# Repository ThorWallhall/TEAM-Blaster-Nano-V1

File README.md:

# T.E.A.M. Blaster Nano V1

**Open-source prop electronics kit for makers, cosplayers, and fandom builders.**  
**Open-Source-Elektronikkit für Maker, Cosplayer und Fandom-Bastler.**

[🇬🇧 English](#english) · [🇩🇪 Deutsch](#deutsch)

---

## English

### Overview

The T.E.A.M. Blaster Nano V1 is a compact all-in-one electronics board for
button-triggered sound and light effects in DIY props — fandom blasters,
sci-fi phasers, lightsabers and similar projects. A single button press plays
an audio sample through the onboard DFPlayer Mini while flashing an LED in sync.

### Features

- Button-triggered audio playback with synchronized LED effect
- Integrated Li-Ion battery charging over USB-C (**TP4056**)
- Battery protection circuit (**DW01A + FS8205A** dual MOSFET)
- Boost converter for a stable supply rail (**MT3608**)
- **ATmega328P-AU** microcontroller — Arduino Nano compatible
- Onboard USB-UART bridge (**CH340G**) — flash firmware directly via USB-C
- Compact form factor with JST-XH connectors for battery, speaker, button, LED

### Hardware

| Block               | Part                     | Package       |
|---------------------|--------------------------|---------------|
| Microcontroller     | ATmega328P-AU            | TQFP-32       |
| Audio player        | DFPlayer Mini (DFR0299)  | module        |
| Battery charger     | TP4056                   | SOIC-8-1EP    |
| Battery protection  | DW01A + FS8205A          | SOT-23-6 + TSSOP-8 |
| Boost converter     | MT3608                   | SOT-23-6      |
| USB-UART bridge     | CH340G                   | SOIC-16       |
| USB input           | USB-C (GCT USB4085)      | —             |

Full bill of materials in `Dokumentation/`.

### Repository Structure

```
├── Code T.E.A.M. - Blaster Nano V1/   → firmware (PlatformIO / Arduino)
├── Dokumentation/                     → BOM, datasheets
├── KiCAD/                             → schematic + PCB design files
├── ASSEMBLY.md                        → ⚠️ assembly & safety notes
└── README.md                          → this file
```

### Firmware

Written in C++11 for the Arduino framework. Builds with either the Arduino IDE
or PlatformIO.

Dependencies:

- `Arduino.h` *(core)*
- `SoftwareSerial.h` *(core)*
- `DFRobotDFPlayerMini` *(install via library manager)*

### ⚠️ Assembly

**Before first power-on, read [`ASSEMBLY.md`](ASSEMBLY.md).**
It contains critical polarity information for the JST-XH connectors —
wrong polarity can destroy the battery cell or the protection circuit.

### License

MIT License — see the `LICENSE` file for details.

### Author

T.E.A.M. — *for your fandom* · © 2026

---

## Deutsch

### Überblick

Der T.E.A.M. Blaster Nano V1 ist eine kompakte All-in-One-Elektronikplatine
für taster-ausgelöste Sound- und Lichteffekte in Eigenbau-Props — Fandom-Blaster,
Sci-Fi-Phaser, Lichtschwerter und ähnliche Projekte. Ein Tastendruck spielt ein
Audio-Sample über das integrierte DFPlayer-Mini-Modul und lässt synchron dazu
eine LED aufleuchten.

### Funktionen

- Taster-ausgelöste Audio-Wiedergabe mit synchronem LED-Effekt
- Integrierte Li-Ion-Akkuladung über USB-C (**TP4056**)
- Schutzschaltung für den Akku (**DW01A + FS8205A** Dual-MOSFET)
- Step-Up-Wandler für stabile Versorgungsspannung (**MT3608**)
- **ATmega328P-AU** Mikrocontroller — Arduino-Nano-kompatibel
- Integrierter USB-UART-Bridge (**CH340G**) — Firmware direkt über USB-C flashen
- Kompaktes Format mit JST-XH-Steckern für Akku, Lautsprecher, Taster, LED

### Hardware

| Block               | Bauteil                  | Gehäuse       |
|---------------------|--------------------------|---------------|
| Mikrocontroller     | ATmega328P-AU            | TQFP-32       |
| Audio-Player        | DFPlayer Mini (DFR0299)  | Modul         |
| Akku-Lader          | TP4056                   | SOIC-8-1EP    |
| Akku-Schutz         | DW01A + FS8205A          | SOT-23-6 + TSSOP-8 |
| Step-Up-Wandler     | MT3608                   | SOT-23-6      |
| USB-UART-Bridge     | CH340G                   | SOIC-16       |
| USB-Eingang         | USB-C (GCT USB4085)      | —             |

Die vollständige Stückliste liegt im Ordner `Dokumentation/`.

### Repository-Struktur

```
├── Code T.E.A.M. - Blaster Nano V1/   → Firmware (PlatformIO / Arduino)
├── Dokumentation/                     → Stückliste, Datenblätter
├── KiCAD/                             → Schaltplan + PCB-Entwurfsdaten
├── ASSEMBLY.md                        → ⚠️ Montage- & Sicherheitshinweise
└── README.md                          → diese Datei
```

### Firmware

Geschrieben in C++11 für das Arduino-Framework. Lässt sich sowohl mit der
Arduino IDE als auch mit PlatformIO bauen.

Abhängigkeiten:

- `Arduino.h` *(Kern)*
- `SoftwareSerial.h` *(Kern)*
- `DFRobotDFPlayerMini` *(über Library Manager installieren)*

### ⚠️ Montage

**Vor dem ersten Einschalten unbedingt [`ASSEMBLY.md`](ASSEMBLY.md) lesen.**
Dort stehen wichtige Polungshinweise zu den JST-XH-Steckern —
falsche Polung kann den Akku oder die Schutzschaltung zerstören.

### Lizenz

MIT-Lizenz — Details in der Datei `LICENSE`.

### Autor

T.E.A.M. — *for your fandom* · © 2026

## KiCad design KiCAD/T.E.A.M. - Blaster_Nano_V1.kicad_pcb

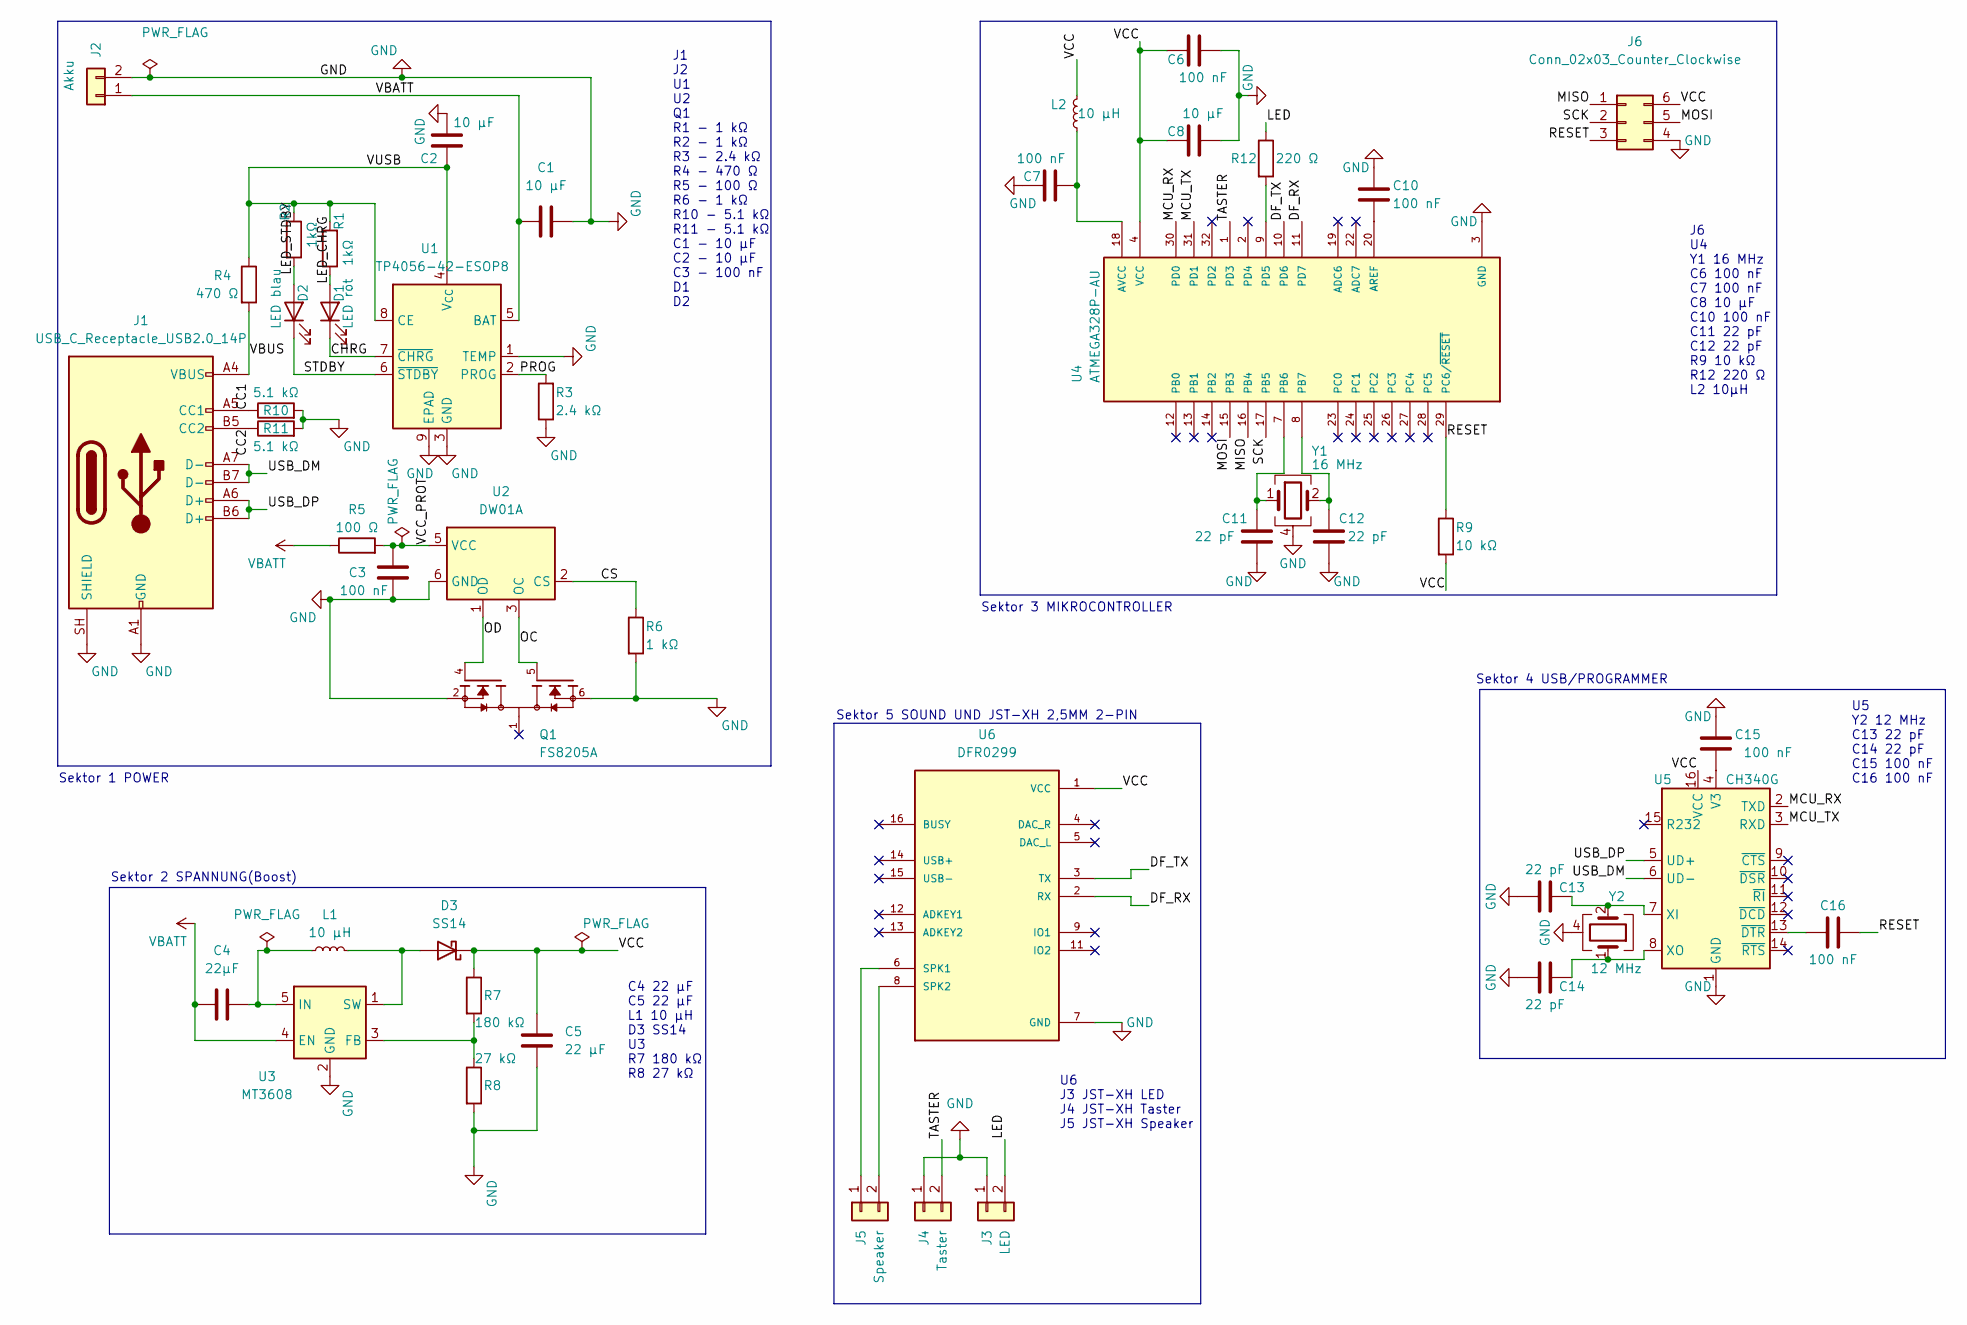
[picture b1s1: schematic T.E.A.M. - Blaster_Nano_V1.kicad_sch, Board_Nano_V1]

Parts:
C1, C2, C8: 10 µF; C_0805_2012Metric
C3, C6, C7, C10, C15, C16: 100 nF; C_0402_1005Metric
C4: 22µF; C_0805_2012Metric
C5: 22 µF; C_0805_2012Metric
C11, C12, C13, C14: 22 pF; C_0402_1005Metric
D1: LED rot; LED_0805_2012Metric
D2: LED blau; LED_0805_2012Metric
D3: SS14; D_SMA
J1: USB_C_Receptacle_USB2.0_14P; USB_C_Receptacle_GCT_USB4085
J2: Akku; JST_XH_B2B-XH-A_1x02_P2.50mm_Vertical
J3: LED; JST_XH_B2B-XH-A_1x02_P2.50mm_Vertical
J4: Taster; JST_XH_B2B-XH-A_1x02_P2.50mm_Vertical
J5: Speaker; JST_XH_B2B-XH-A_1x02_P2.50mm_Vertical
J6: Conn_02x03_Counter_Clockwise; PinHeader_2x03_P2.54mm_Vertical
L1, L2: 10 µH; L_0805_2012Metric
Q1: FS8205A; TSSOP-8_4.4x3mm_P0.65mm; PARTREV 1.7
R1, R2: 1kΩ; R_0402_1005Metric
R3: 2.4 kΩ; R_0402_1005Metric
R4: 470 Ω; R_0402_1005Metric
R5: 100 Ω; R_0402_1005Metric
R6: 1 kΩ; R_0402_1005Metric
R7: 180 kΩ; R_0402_1005Metric
R8: 27 kΩ; R_0402_1005Metric
R9: 10 kΩ; R_0402_1005Metric
R10, R11: 5.1 kΩ; R_0402_1005Metric
R12: 220 Ω
U1: TP4056-42-ESOP8; SOIC-8-1EP_3.9x4.9mm_P1.27mm_EP2.41x3.3mm_ThermalVias
U2: DW01A; SOT-23-6
U3: MT3608; SOT-23-6
U4: ATMEGA328P-AU; QFP80P900X900X120-32N; PARTREV 8271A
U5: CH340G; SOIC-16_3.9x9.9mm_P1.27mm
U6: DFR0299; MODULE_DFR0299
Y1: 16 MHz; Crystal_SMD_3225-4Pin_3.2x2.5mm
Y2: 12 MHz; Crystal_SMD_3225-4Pin_3.2x2.5mm

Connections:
/CC1: J1.A5 (CC1), R10.1
/CC2: J1.B5 (CC2), R11.1
/CHRG: D1.1 (K), U1.7 (~CHRG)
/CS: R6.1, U2.2 (CS)
/DF_RX: U4.11 (PD7), U6.2 (RX)
/DF_TX: U4.10 (PD6), U6.3 (TX)
/LED: J3.2, R12.1
/LED_CHRG: D1.2 (A), R1.1
/LED_STDBY: D2.2 (A), R2.2
/MCU_RX: U4.30 (PD0), U5.2 (TXD)
/MCU_TX: U4.31 (PD1), U5.3 (RXD)
/MISO: J6.1, U4.16 (PB4)
/MOSI: J6.5, U4.15 (PB3)
/OC: Q1.5, U2.3 (OC)
/OD: Q1.4, U2.1 (OD)
/PROG: R3.2, U1.2 (PROG)
/RESET: C16.2, J6.3, R9.1, U4.29 (PC6/~RESET)
/SCK: J6.2, U4.17 (PB5)
/STDBY: D2.1 (K), U1.6 (~STDBY)
/TASTER: J4.2, U4.1 (PD3)
/USB_DM: J1.A7 (D-), J1.B7 (D-), U5.6 (UD-)
/USB_DP: J1.A6 (D+), J1.B6 (D+), U5.5 (UD+)
/VBUS: J1.A4 (VBUS), J1.A9 (VBUS), J1.B4 (VBUS), J1.B9 (VBUS), R4.2
/VCC_PROT: C3.1, R5.2, U2.5 (VCC)
/VUSB: C2.2, R1.2, R2.1, R4.1, U1.4 (V_{CC}), U1.8 (CE)
GND: C1.2, C2.1, C3.2, C5.2, C6.2, C7.1, C8.2, C10.1, C11.2, C12.2, C13.1, C14.1, C15.1, J1.A1 (GND), J1.A12 (GND), J1.B1 (GND), J1.B12 (GND), J1.SH (SHIELD), J2.2, J3.1, J4.1, J6.4, Q1.2, Q1.3, Q1.6, Q1.7, R3.1, R6.2, R8.2, R10.2, R11.2, U1.1 (TEMP), U1.3 (GND), U1.9 (EPAD), U2.6 (GND), U3.2 (GND), U4.3 (GND), U4.5 (GND), U4.21 (GND), U5.1 (GND), U6.7 (GND), U6.10 (GND), Y1.3 (G), Y1.4 (G), Y2.3 (G), Y2.4 (G)
unnamed: D3.2 (A), L1.2, U3.1 (SW)
unnamed: J5.1, U6.6 (SPK1)
unnamed: J5.2, U6.8 (SPK2)
unnamed: R7.2, R8.1, U3.3 (FB)
unnamed: C4.2, L1.1, U3.5 (IN)
unnamed: C10.2, U4.20 (AREF)
unnamed: C7.2, L2.1, U4.18 (AVCC)
unnamed: C11.1, U4.7 (PB6), Y1.1
unnamed: C12.1, U4.8 (PB7), Y1.2 (4)
unnamed: R12.2, U4.9 (PD5)
unnamed: C15.2, U5.4 (V3)
unnamed: C13.2, U5.7 (XI), Y2.2 (4)
unnamed: C14.2, U5.8 (XO), Y2.1
unnamed: C16.1, U5.13 (~DTR)
VBATT: C1.1, C4.1, J2.1, R5.1, U1.5 (BAT), U3.4 (EN)
VCC: C5.1, C6.1, C8.1, D3.1 (K), J6.6, L2.2, R7.1, R9.2, U4.4 (VCC), U4.6 (VCC), U5.16 (VCC), U6.1 (VCC)

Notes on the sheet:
Sektor 5 SOUND UND JST-XH 2,5MM 2-PIN
Sektor 4 USB/PROGRAMMER
C4 22 µF C5 22 µF L1 10 µH D3 SS14 U3 R7 180 kΩ R8 27 kΩ
U5 Y2 12 MHz C13 22 pF C14 22 pF C15 100 nF C16 100 nF
U6 J3 JST-XH LED J4 JST-XH Taster J5 JST-XH Speaker
Sektor 1 POWER
Sektor 3 MIKROCONTROLLER
J1 J2 U1 U2 Q1 R1 - 1 kΩ R2 - 1 kΩ R3 - 2.4 kΩ R4 - 470 Ω R5 - 100 Ω R6 - 1 kΩ R10 - 5.1 kΩ R11 - 5.1 kΩ C1 - 10 µF C2 - 10 µF C3 - 100 nF D1 D2
Sektor 2 SPANNUNG(Boost)
J6 U4 Y1 16 MHz C6 100 nF C7 100 nF C8 10 µF C10 100 nF C11 22 pF C12 22 pF R9 10 kΩ R12 220 Ω L2 10µH

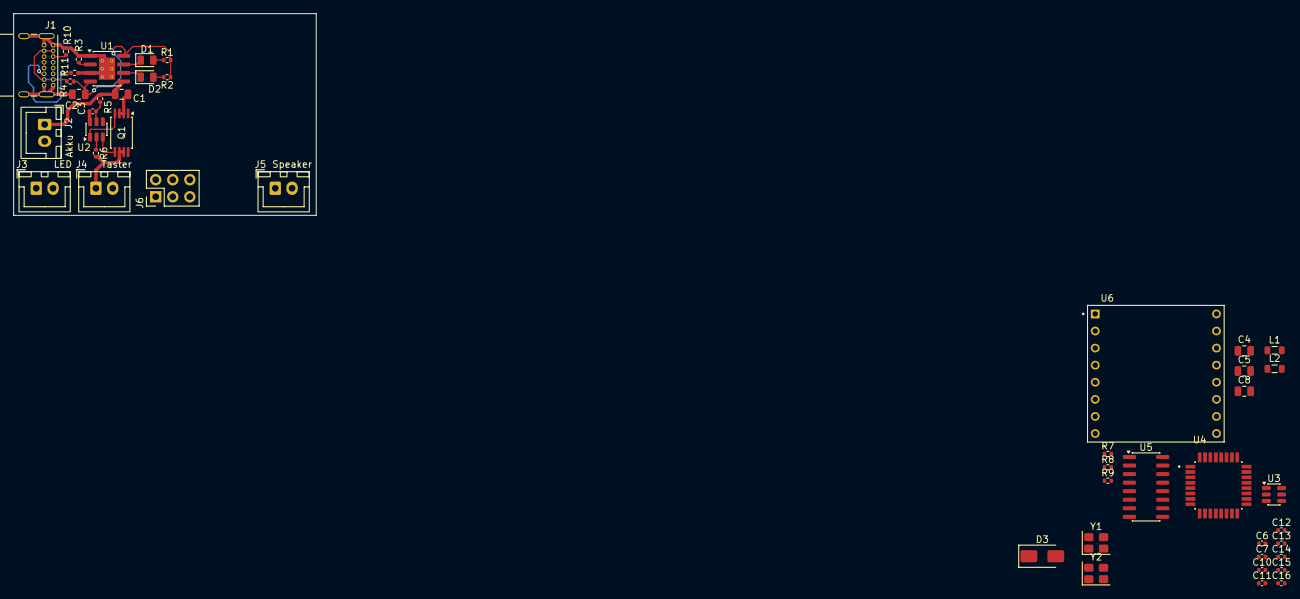
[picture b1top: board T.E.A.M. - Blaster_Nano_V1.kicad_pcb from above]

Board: 2 copper layers, 45.0 x 30.0 mm, 46 parts (0 on the bottom side), 40 nets.

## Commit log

2026-04-16 Initial Commit - T.E.A.M. Blaster Nano V1
2026-04-16 Update platformio.ini: change board type to nanoatmega328new and increase upload speed to 115200
2026-04-16 Update: .gitignore ergänzt
2026-04-16 Fix: .gitignore Leerzeichen entfernt
2026-04-17 KiCAD Sektor 1 POWER - Bauteile platziert, J2 verdrahtet.
2026-04-17 Sektor 1 POWER - DW01A verdrahtet.
2026-04-17 Update: .gitignore KiCAD Backups und Lock Dateien ignorieren.
2026-04-17 Cleanup: Backup und Lock Dateien entfernt.
2026-04-17 Sektor 1 POWER -vollständig verdrahtet und eingerahmt.
2026-04-17 Sektor 2 SPANNUNG - MT3608 fertig verdrahtet.
2026-04-17 Sektor 3 MIKROCONTROLLER - ATmega328P-Au und 6 Pinheader verdrahtet.
2026-04-17 Sektor 4 USB/PROGRAMMER - CH340G verdrahtet.
2026-04-17 Sektor 5 SOUND UND JST-XH 2,5MM 2-PIN verdrahtet.
2026-04-17 ERC bereinigt - 0 Fehler, 4 Footprints Warnungen.
2026-04-17 Netzklassen erstellt und zugeordnet.
2026-04-17 Footprints zugewiesen - alle Bauteile komplett.
2026-04-17 BOM erstellt und heruntergeladen.
2026-04-18 .gitignore erweitert: kicad_prl und Tilde-Lock_Dateien ausgeschlossen
2026-04-18 Add assembly instructions and safety warnings
    Document important assembly information and safety checks for the T.E.A.M. Blaster Nano V1.
2026-04-18 Add README for T.E.A.M. Blaster Nano V1
    Added detailed information about the T.E.A.M. Blaster Nano V1, including features, hardware specifications, repository structure, firmware details, assembly instructions, and licensing.
2026-04-18 Fix schematic pin numbers (J2-J5) and footprint references (Q1, Y1, Y2, U6)
2026-04-18 Add Crystal_GND31 symbol and connect crystal shield to GND
2026-04-18 Add 3D models for U1, U4, U6
2026-04-18 Add Aisler 2-layer HASL design rules
2026-04-18 Add fiducial markers for SMD assembly
2026-04-18 Set net class trace widths (Power 0.5mm, USB 0.2mm)
2026-04-18 Add GND copper zones on F.Cu and B.Cu
2026-04-18 PCB Routing Zwischenstand
2026-04-19 Schaltplan finalisiert: alle Sektoren abgeschlossen
2026-04-19 gitignore erweitert: Excel temp und Report-Dateien ausgeschlossen
2026-04-19 Sektor 1: Placement und Routing abgeschlossen
